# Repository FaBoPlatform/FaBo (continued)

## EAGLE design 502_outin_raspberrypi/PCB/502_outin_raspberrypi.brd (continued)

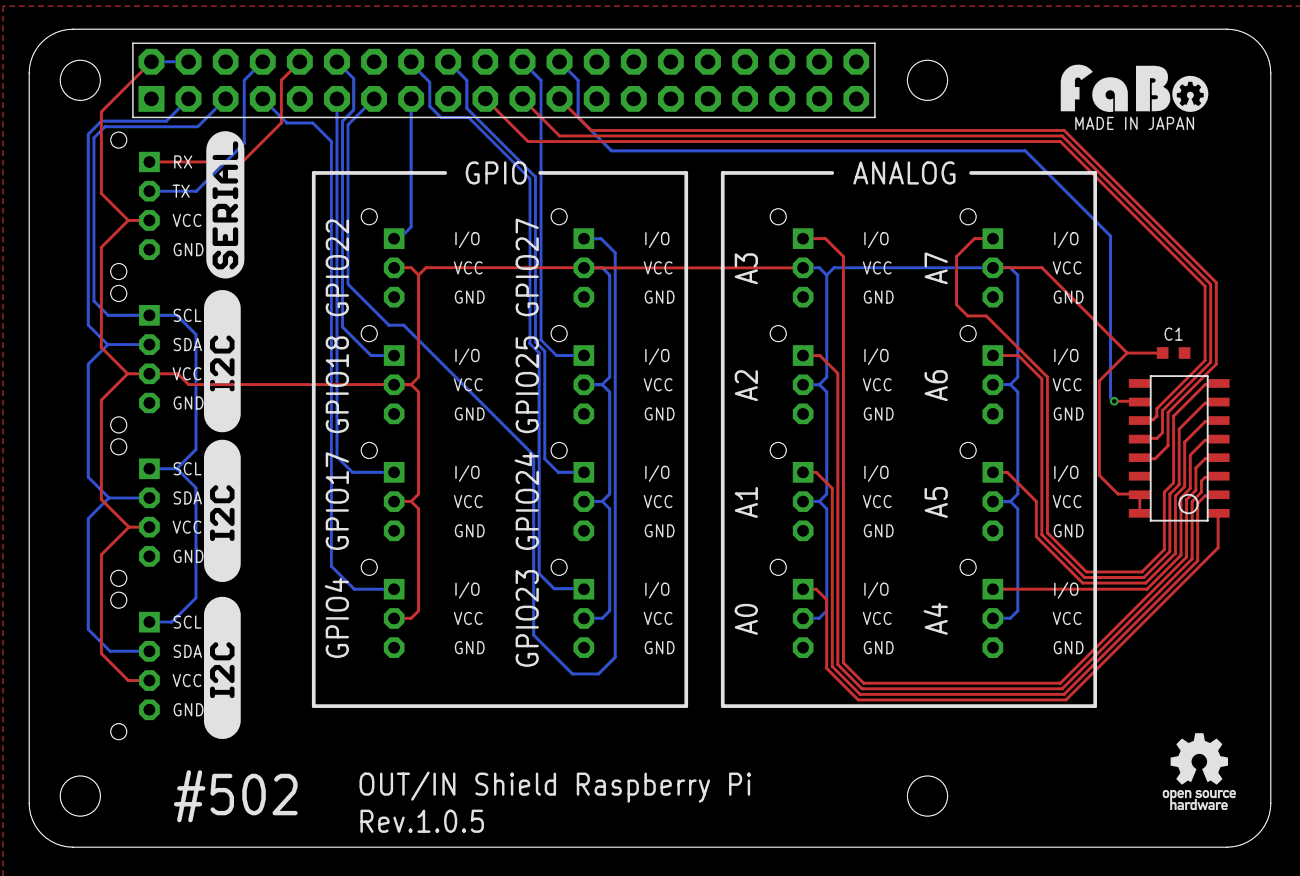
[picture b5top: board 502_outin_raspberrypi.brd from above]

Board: 2 copper layers, 85.0 x 56.0 mm, 29 parts (0 on the bottom side), 26 nets.

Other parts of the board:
U$2, U$5, U$6: LOGO_SILK_I2C
U$3: LOGO_SILK_SERIAL2

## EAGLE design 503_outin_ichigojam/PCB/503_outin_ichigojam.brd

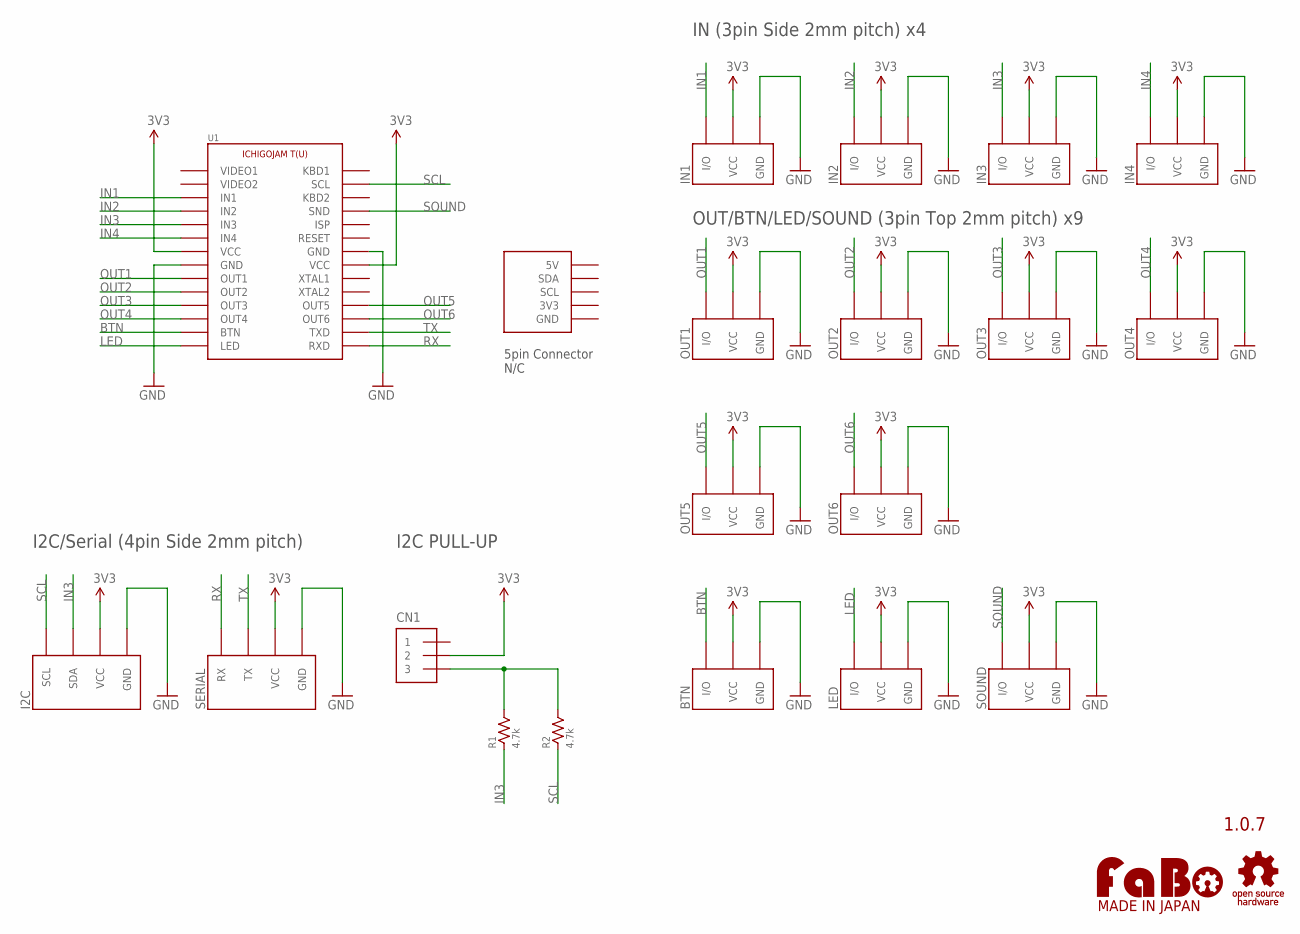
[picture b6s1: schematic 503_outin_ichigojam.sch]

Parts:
BTN: FABO_BRICK_3PIN-B03B-PASK-1; FABO_BRICK_3PIN_B03B-PASK-1
CN1: PIN_HEADER_1X3; PIN_1X3
I2C: FABO_BRICK_I2C-S04B-PASK-2_LONG; FABO_BRICK_I2C_S04B-PASK-2_LONG
IN1, IN2, IN3, IN4: FABO_BRICK_3PIN-S03B-PASK-2_LONG; FABO_BRICK_3PIN_S03B-PASK-2_LONG
LED: FABO_BRICK_3PIN-B03B-PASK-1; FABO_BRICK_3PIN_B03B-PASK-1
OUT1, OUT2, OUT3, OUT4, OUT5, OUT6: FABO_BRICK_3PIN-B03B-PASK-1; FABO_BRICK_3PIN_B03B-PASK-1
R1, R2: 4.7k; AXL-REGULAR
SERIAL: FABO_BRICK_SERIAL-S04B-PASK-2_LONG; FABO_BRICK_SERIAL_S04B-PASK-2_LONG
SOUND: FABO_BRICK_3PIN-B03B-PASK-1; FABO_BRICK_3PIN_B03B-PASK-1
U1: ICHIGOJAM_T-NOLABEL; ICHIGOJAM_T_NOLABEL
U$2: LOGO_OSHW-M_BOTTOM; LOGO_OSHW_M_BOTTOM
U$3: LOGO_FABO-M; LOGO_FABO_MS

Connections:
3V3: BTN.VCC, CN1.2, I2C.VCC, IN1.VCC, IN2.VCC, IN3.VCC, IN4.VCC, LED.VCC, OUT1.VCC, OUT2.VCC, OUT3.VCC, OUT4.VCC, OUT5.VCC, OUT6.VCC, SERIAL.VCC, SOUND.VCC, U1.VCC1 (VCC), U1.VCC2 (VCC)
BTN: BTN.I/O, U1.BTN
GND: BTN.GND, I2C.GND, IN1.GND, IN2.GND, IN3.GND, IN4.GND, LED.GND, OUT1.GND, OUT2.GND, OUT3.GND, OUT4.GND, OUT5.GND, OUT6.GND, SERIAL.GND, SOUND.GND, U1.GND1 (GND), U1.GND2 (GND)
IN1: IN1.I/O, U1.IN1
IN2: IN2.I/O, U1.IN2
IN3: I2C.SDA, IN3.I/O, R1.1, U1.IN3
IN4: IN4.I/O, U1.IN4
LED: LED.I/O, U1.LED
unnamed: CN1.3, R1.2, R2.2
OUT1: OUT1.I/O, U1.OUT1
OUT2: OUT2.I/O, U1.OUT2
OUT3: OUT3.I/O, U1.OUT3
OUT4: OUT4.I/O, U1.OUT4
OUT5: OUT5.I/O, U1.OUT5
OUT6: OUT6.I/O, U1.OUT6
RX: SERIAL.RX, U1.RXD
SCL: I2C.SCL, R2.1, U1.SCL1 (SCL)
SOUND: SOUND.I/O, U1.SND
TX: SERIAL.TX, U1.TXD

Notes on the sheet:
1.0.7
IN (3pin Side 2mm pitch) x4
OUT/BTN/LED/SOUND (3pin Top 2mm pitch) x9
I2C/Serial (4pin Side 2mm pitch)
I2C PULL-UP
5pin Connector N/C

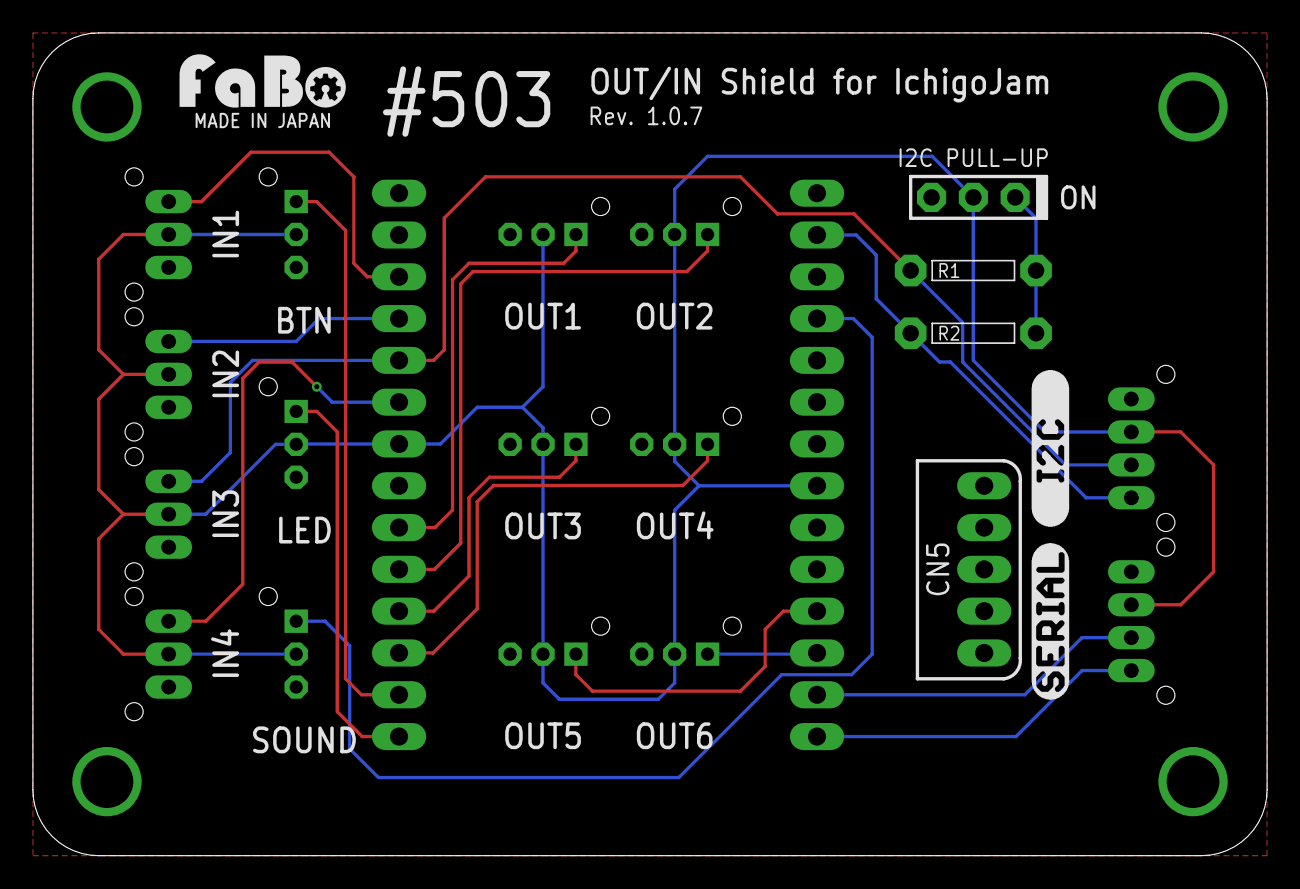
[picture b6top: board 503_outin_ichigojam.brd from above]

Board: 2 copper layers, 75.0 x 50.0 mm, 23 parts (0 on the bottom side), 19 nets.

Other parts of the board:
U$4: LOGO_SILK_I2C
U$5: LOGO_SILK_SERIAL2

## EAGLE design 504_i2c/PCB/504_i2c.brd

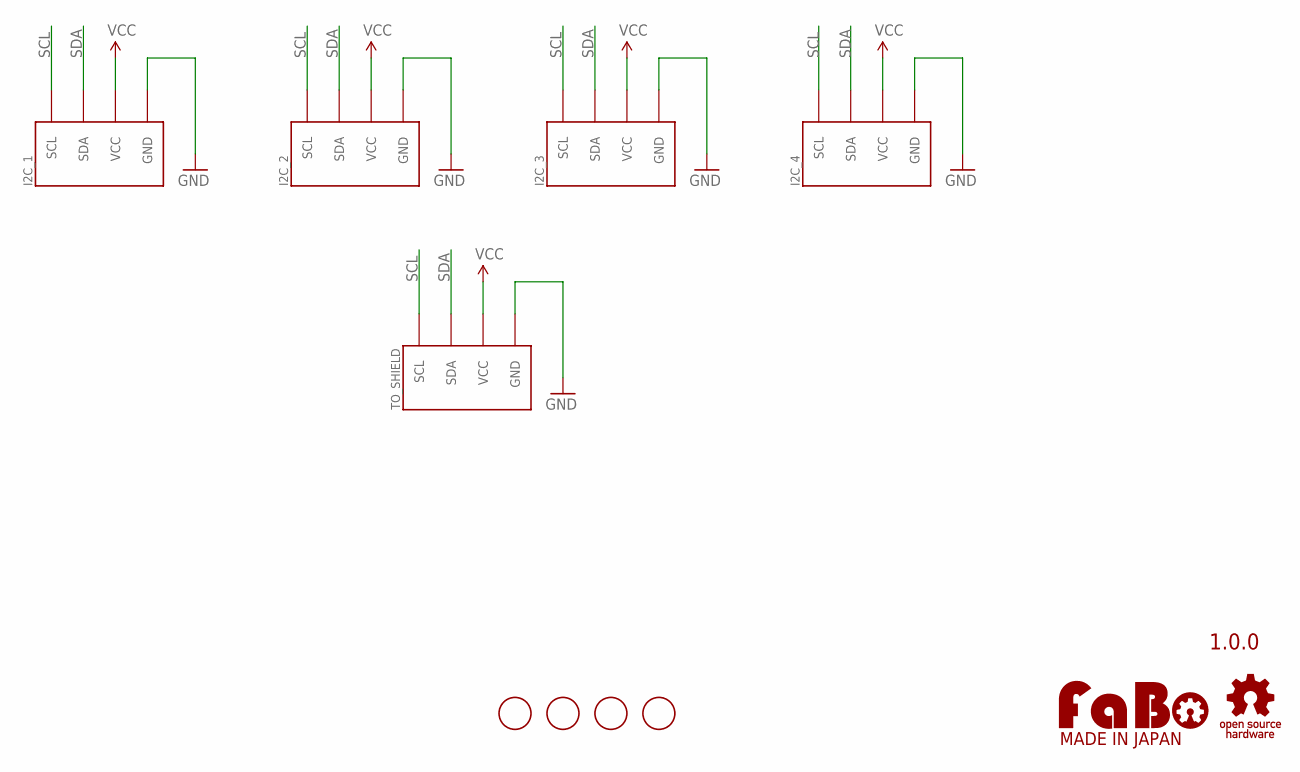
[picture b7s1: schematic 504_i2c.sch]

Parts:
I2C_1, I2C_2, I2C_3, I2C_4: FABO_BRICK_I2C-CONNECTOR; FABO_BRICK_I2C_CONNECTOR
TO_SHIELD: FABO_BRICK_I2C-CONNECTOR; FABO_BRICK_I2C_CONNECTOR
U$7, U$8, U$9, U$10: SCREW-PAD-3MM; SCREWPAD_3MM
U$11: LOGO_OSHW-T_M; LOGO_OSHW_T_M
U$12: LOGO_FABO-M; LOGO_FABO_M

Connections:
GND: I2C_1.GND, I2C_2.GND, I2C_3.GND, I2C_4.GND, TO_SHIELD.GND
SCL: I2C_1.SCL, I2C_2.SCL, I2C_3.SCL, I2C_4.SCL, TO_SHIELD.SCL
SDA: I2C_1.SDA, I2C_2.SDA, I2C_3.SDA, I2C_4.SDA, TO_SHIELD.SDA
VCC: I2C_1.VCC, I2C_2.VCC, I2C_3.VCC, I2C_4.VCC, TO_SHIELD.VCC

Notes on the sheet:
1.0.0

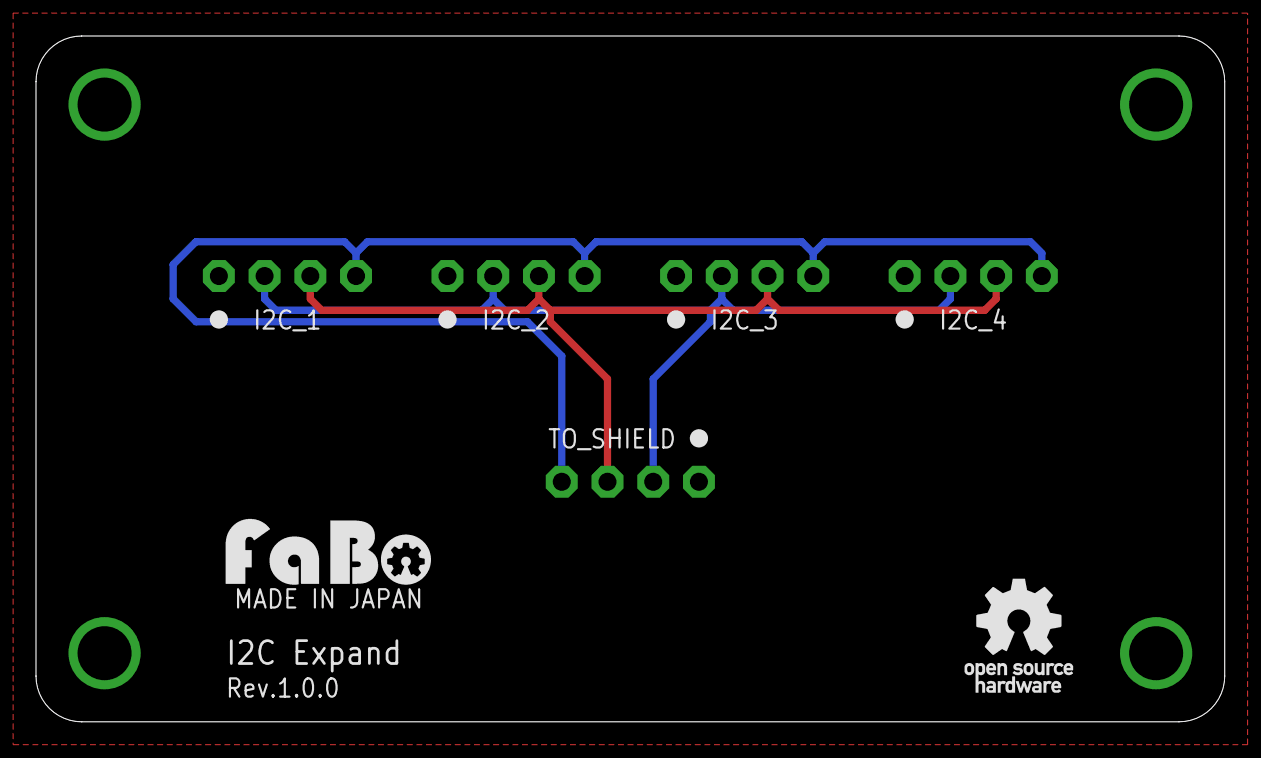
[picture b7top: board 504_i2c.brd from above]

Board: 2 copper layers, 66.0 x 38.1 mm, 11 parts (0 on the bottom side), 4 nets.
